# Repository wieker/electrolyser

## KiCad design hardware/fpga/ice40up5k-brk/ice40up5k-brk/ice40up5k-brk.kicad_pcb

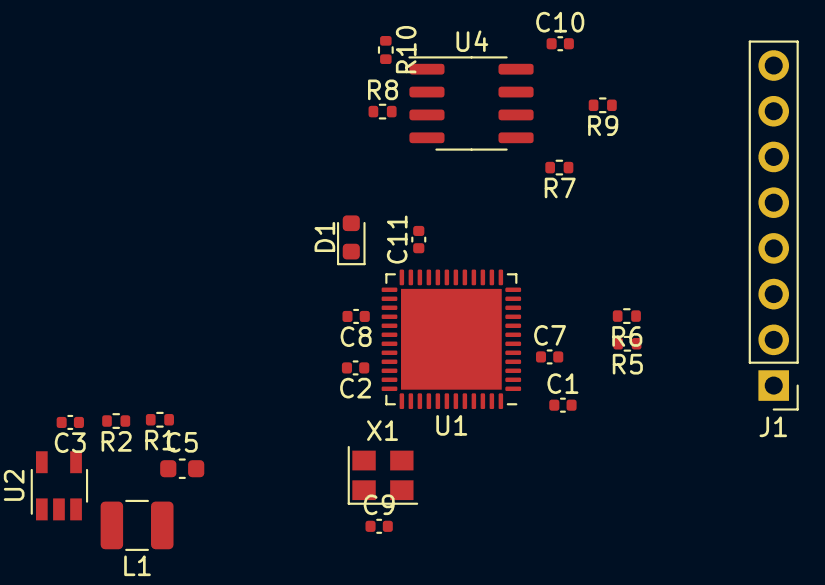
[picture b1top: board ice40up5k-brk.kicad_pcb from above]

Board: 2 copper layers, 24 parts (0 on the bottom side), 13 nets, no tracks yet.

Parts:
C1, C2, C7, C8, C10, C11: 0.1uF; C_0402_1005Metric
C3: 4.7uF; C_0402_1005Metric
C5: 10uF; C_0603_1608Metric
C9: 0.01uF; C_0402_1005Metric
D1: CDBU0520; D_0603_1608Metric
J1: Conn_01x08_Male; PinHeader_1x08_P2.54mm_Vertical
L1: L; L_1210_3225Metric
R1, R2, R5, R6, R7, R8, R9, R10: 100kOhm; R_0402_1005Metric
U1: ICE40UP5K-SG48ITR; QFN-48-1EP_7x7mm_P0.5mm_EP5.6x5.6mm
U2: LTC3406ES5; TSOT-23-5
U4: AT25SF081-SSHD-X; SOIC-8_3.9x4.9mm_P1.27mm
X1: ASE-xxxMHz; Oscillator_SMD_Abracon_ASE-4Pin_3.2x2.5mm

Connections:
+1V2: C5.1, C7.1, C8.1, L1.1, R1.1, U1.5, U1.29, U1.30
+3V3: C1.1, C2.1, C3.1, C9.1, C10.1, C11.1, D1.2, J1.1, R5.1, R6.1, R7.1, R8.1, R9.1, R10.1, U1.1, U1.22, U1.33, U2.1, U2.4, U4.8, X1.1, X1.4
GND: C1.2, C2.2, C3.2, C5.2, C7.2, C8.2, C9.2, C10.2, C11.2, J1.8, R2.2, U1.49, U2.2, U4.4, X1.2
unnamed: D1.1, U1.24
unnamed: L1.2, U2.3
unnamed: R1.2, R2.1, U2.5
cdone: J1.2, R5.2, U1.7
clk: U1.37, X1.3
creset: J1.3, R6.2, U1.8
miso: J1.6, R8.2, U1.14, U4.2
mosi: J1.7, R7.2, U1.17, U4.5
sck: J1.4, R9.2, U1.15, U4.6
ss: J1.5, R10.2, U1.16, U4.1

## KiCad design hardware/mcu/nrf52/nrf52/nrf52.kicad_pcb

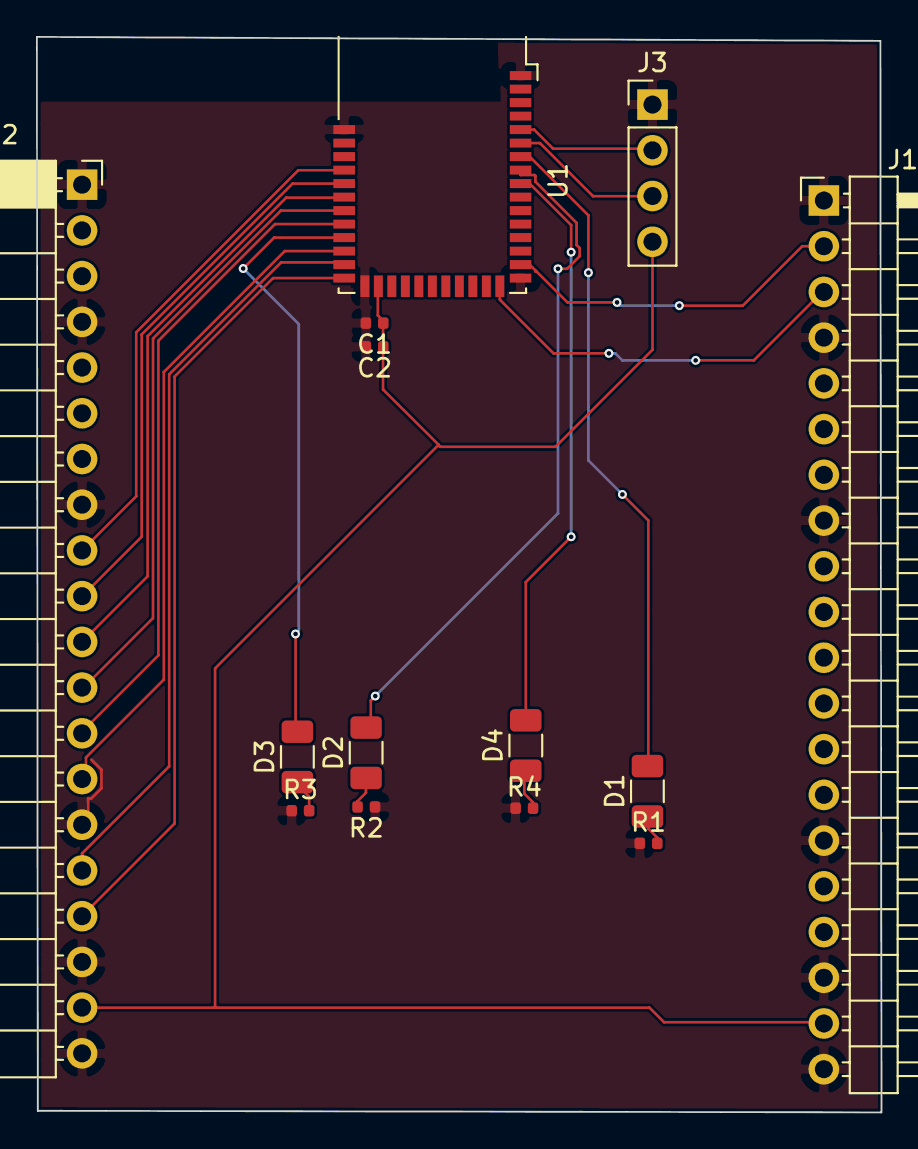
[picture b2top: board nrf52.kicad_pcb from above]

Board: 2 copper layers, 46.9 x 59.8 mm, 14 parts (0 on the bottom side), 22 nets.

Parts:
C1: 0.1uF; C_0402_1005Metric
C2: 4.7uF; C_0402_1005Metric
D1, D2, D3, D4: LED; C_1206_3216Metric
J1: Conn_01x20_Female; PinHeader_1x20_P2.54mm_Horizontal
J2: Conn_01x20_Male; PinSocket_1x20_P2.54mm_Horizontal
J3: Conn_01x04_Male; PinHeader_1x04_P2.54mm_Vertical
R1, R2, R3, R4: 10kOhm; R_0402_1005Metric
U1: BL652; Laird_BL652

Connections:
+3V3: C1.1, C2.1, J1.19, J2.19, J3.4, U1.26
GND: C1.2, C2.2, J1.1, J1.4, J1.8, J1.15, J1.18, J1.20, J2.1, J2.4, J2.8, J2.15, J2.18, J2.20, J3.1, R1.1, R2.1, R3.1, R4.1, U1.1, U1.16, U1.27, U1.39
unnamed: D1.1, R1.2
unnamed: D1.2, U1.7
unnamed: D2.1, R2.2
unnamed: D2.2, U1.8
unnamed: D3.1, R3.2
unnamed: D3.2, U1.31
unnamed: D4.1, R4.2
unnamed: D4.2, U1.9
unnamed: J1.2, U1.15
unnamed: J1.3, U1.17
unnamed: J2.9, U1.36
unnamed: J2.10, U1.35
unnamed: J2.11, U1.34
unnamed: J2.12, U1.33
unnamed: J2.13, U1.32
unnamed: J2.14, U1.30
unnamed: J2.16, U1.29
unnamed: J2.17, U1.28
unnamed: J3.2, U1.5
unnamed: J3.3, U1.6

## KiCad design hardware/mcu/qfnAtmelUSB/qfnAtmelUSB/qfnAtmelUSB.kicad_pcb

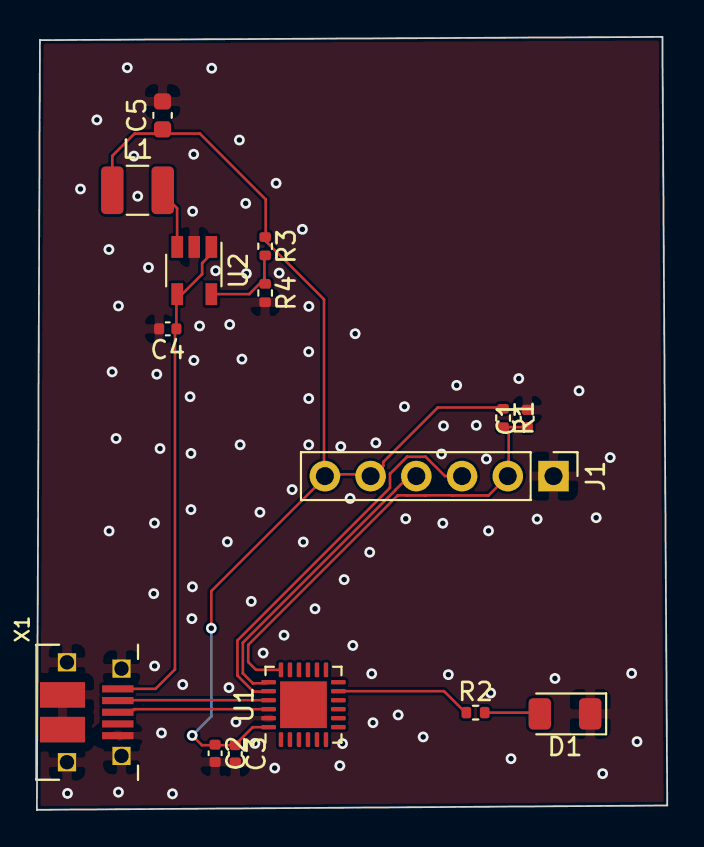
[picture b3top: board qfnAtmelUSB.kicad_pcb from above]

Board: 2 copper layers, 35.0 x 42.9 mm, 15 parts (0 on the bottom side), 12 nets.

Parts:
C1, C3: 0.1uF; C_0402_1005Metric
C2, C4: 4.7uF; C_0402_1005Metric
C5: 10uF; C_0603_1608Metric
D1: LED; LED_1206_3216Metric
J1: Conn_01x06_Male; PinHeader_1x06_P2.54mm_Vertical
L1: L; L_1210_3225Metric
R1, R2: 10kOhm; R_0402_1005Metric
R3: 450kOhm; R_0402_1005Metric
R4: 100kOhm; R_0402_1005Metric
U1: ATSAMD11D14A-M; QFN-24-1EP_4x4mm_P0.5mm_EP2.6x2.6mm
U2: LTC3406ES5; TSOT-23-5
X1: USBFCI_10103594_MILL; FCI_10103594_MILL

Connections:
+3V3: C2.1, C3.1, C5.1, J1.5, J1.6, L1.1, R1.1, R3.1, U1.24
+5V: C4.1, U2.1, U2.4, X1.VBUS
GND: C1.2, C2.2, C3.2, C4.2, C5.2, D1.1, J1.1, R4.2, U1.23, U2.2, X1.BASE@1, X1.BASE@2, X1.GND, X1.SPRT@1, X1.SPRT@2, X1.SPRT@3, X1.SPRT@4
unnamed: D1.2, R2.2
unnamed: L1.2, U2.3
unnamed: R3.2, R4.1, U2.5
unnamed: U1.21, X1.D-
unnamed: U1.22, X1.D+
led_mcu: R2.1, U1.11
swd_clk: J1.4, U1.19
swd_io: J1.3, U1.20
swd_rst: C1.1, J1.2, R1.2, U1.18

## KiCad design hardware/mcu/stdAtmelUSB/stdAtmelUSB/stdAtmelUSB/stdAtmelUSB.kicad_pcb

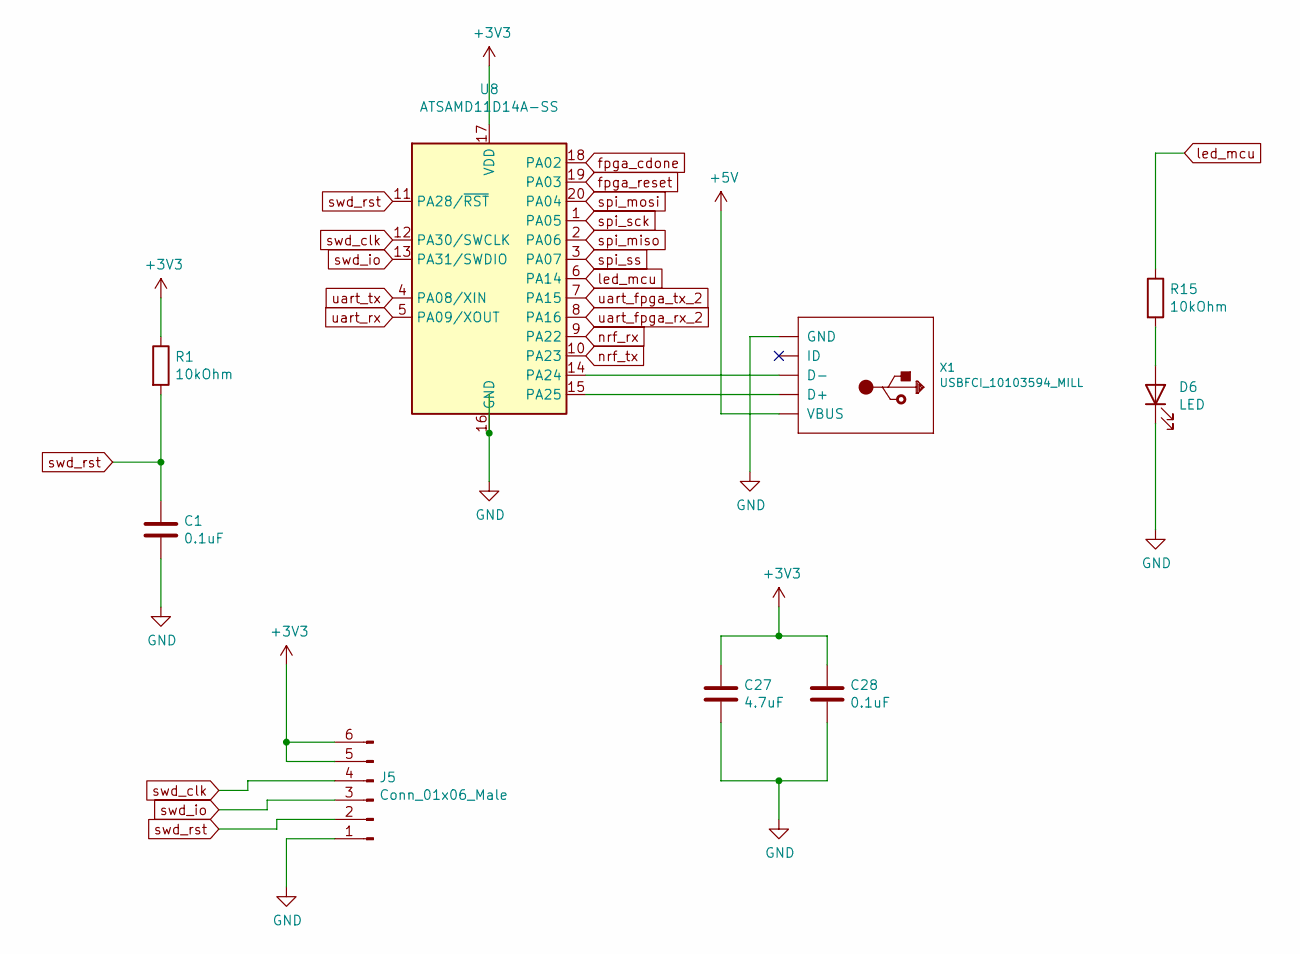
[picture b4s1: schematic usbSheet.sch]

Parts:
C1, C28: 0.1uF; C_0402_1005Metric
C27: 4.7uF; C_0402_1005Metric
D6: LED; LED_1206_3216Metric
J5: Conn_01x06_Male; PinHeader_1x06_P2.54mm_Vertical
R1, R15: 10kOhm; R_0402_1005Metric
U8: ATSAMD11D14A-SS; SOIC-20W_7.5x12.8mm_P1.27mm
X1: USBFCI_10103594_MILL; FCI_10103594_MILL

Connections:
+3V3: C27.1, C28.1, J5.5, J5.6, R1.1, U8.17 (VDD); also elsewhere on the board
+5V: X1.VBUS; also elsewhere on the board
GND: C1.2, C27.2, C28.2, D6.1 (K), J5.1, U8.16 (GND), X1.BASE@1 (GND), X1.BASE@2 (GND), X1.GND, X1.SPRT@1 (GND), X1.SPRT@2 (GND), X1.SPRT@3 (GND), X1.SPRT@4 (GND); also elsewhere on the board
unnamed: D6.2 (A), R15.2
unnamed: U8.14 (PA24), X1.D-
unnamed: U8.15 (PA25), X1.D+
fpga_cdone: U8.18 (PA02); also elsewhere on the board
fpga_reset: U8.19 (PA03); also elsewhere on the board
led_mcu: R15.1, U8.6 (PA14)
nrf_rx: U8.9 (PA22); also elsewhere on the board
nrf_tx: U8.10 (PA23); also elsewhere on the board
spi_miso: U8.2 (PA06); also elsewhere on the board
spi_mosi: U8.20 (PA04); also elsewhere on the board
spi_sck: U8.1 (PA05); also elsewhere on the board
spi_ss: U8.3 (PA07); also elsewhere on the board
swd_clk: J5.4, U8.12 (PA30/SWCLK)
swd_io: J5.3, U8.13 (PA31/SWDIO)
swd_rst: C1.1, J5.2, R1.2, U8.11 (PA28/~RST)
uart_fpga_rx_2: U8.8 (PA16); also elsewhere on the board
uart_fpga_tx_2: U8.7 (PA15); also elsewhere on the board
uart_rx: U8.5 (PA09/XOUT); also elsewhere on the board
uart_tx: U8.4 (PA08/XIN); also elsewhere on the board

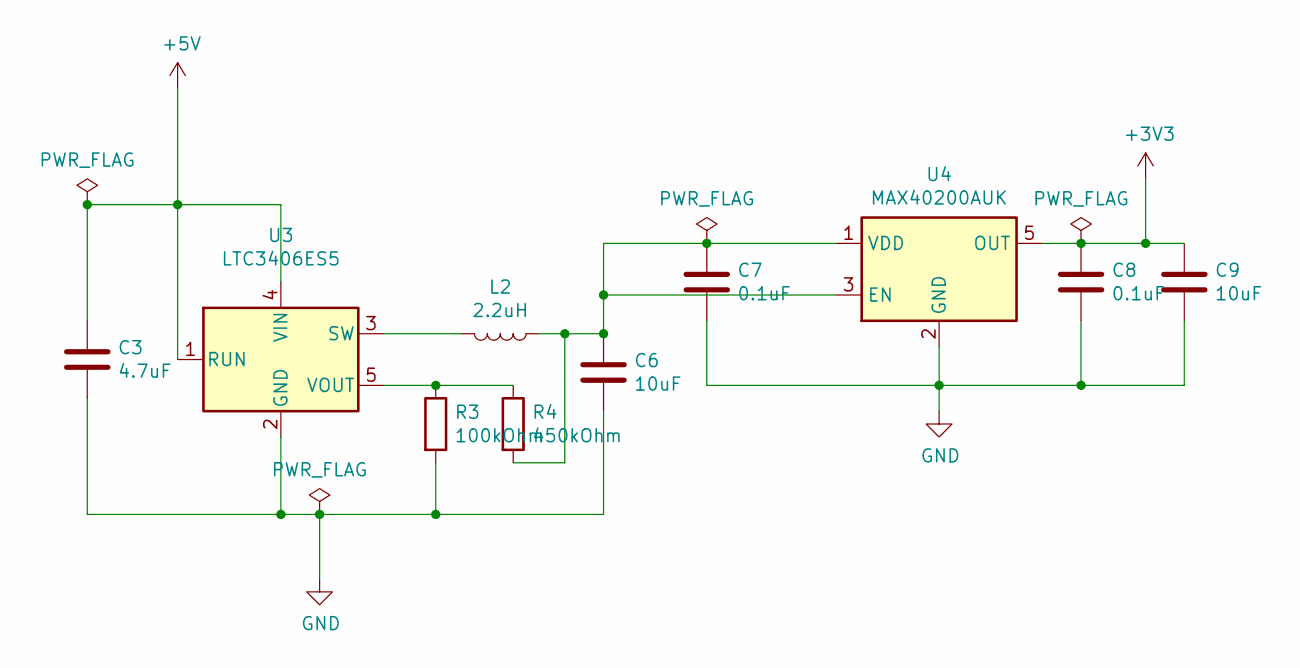
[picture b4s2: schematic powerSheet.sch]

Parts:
C3: 4.7uF; C_0402_1005Metric
C6, C9: 10uF; C_0603_1608Metric
C7, C8: 0.1uF; C_0402_1005Metric
L2: 2.2uH; L_0805_2012Metric
R3: 100kOhm; R_0402_1005Metric
R4: 450kOhm; R_0402_1005Metric
U3: LTC3406ES5; TSOT-23-5
U4: MAX40200AUK; SOT-23-5

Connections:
+3V3: C8.1, C9.1, U4.5 (OUT); also elsewhere on the board
+5V: C3.1, U3.1 (RUN), U3.4 (VIN); also elsewhere on the board
GND: C3.2, C6.2, C7.2, C8.2, C9.2, R3.2, U3.2 (GND), U4.2 (GND); also elsewhere on the board
unnamed: C6.1, C7.1, L2.1, R4.2, U4.1 (VDD), U4.3 (EN)
unnamed: L2.2, U3.3 (SW)
unnamed: R3.1, R4.1, U3.5 (VOUT)

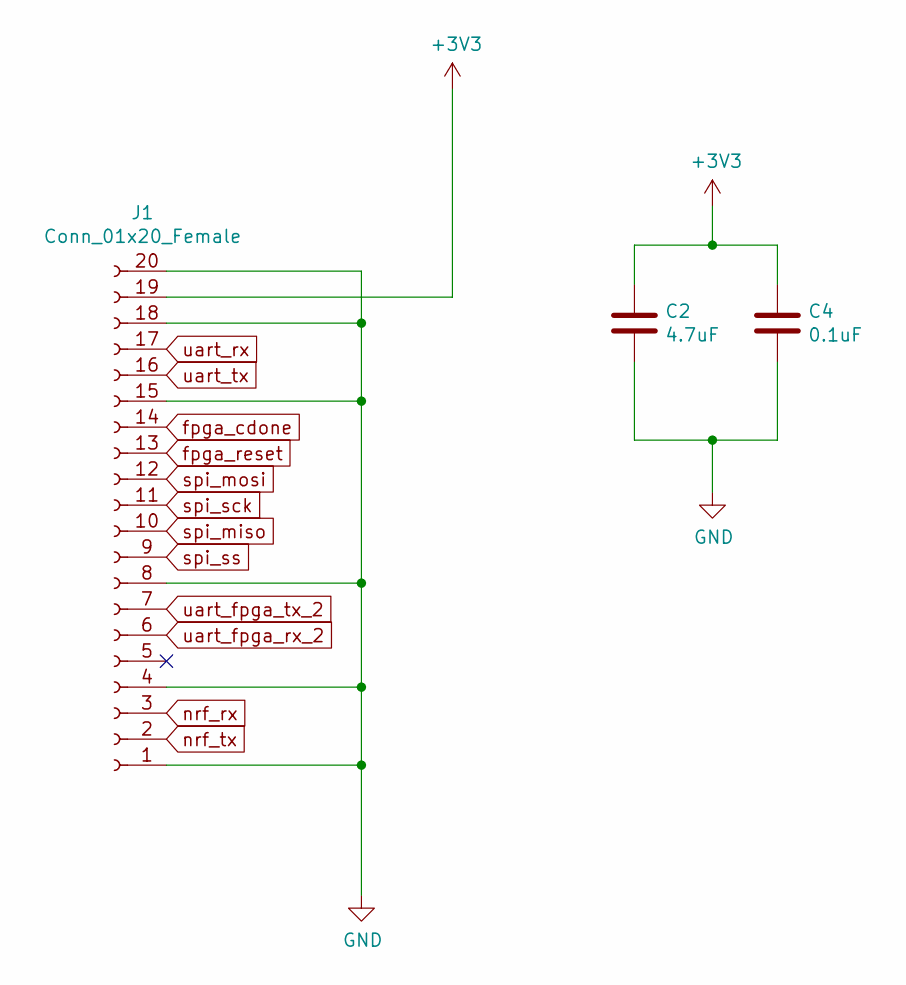
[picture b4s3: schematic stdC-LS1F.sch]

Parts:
C2: 4.7uF; C_0402_1005Metric
C4: 0.1uF; C_0402_1005Metric
J1: Conn_01x20_Female; PinHeader_1x20_P2.54mm_Horizontal

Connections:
+3V3: C2.1, C4.1, J1.19; also elsewhere on the board
GND: C2.2, C4.2, J1.1, J1.4, J1.8, J1.15, J1.18, J1.20; also elsewhere on the board
fpga_cdone: J1.14; also elsewhere on the board
fpga_reset: J1.13; also elsewhere on the board
nrf_rx: J1.3; also elsewhere on the board
nrf_tx: J1.2; also elsewhere on the board
spi_miso: J1.10; also elsewhere on the board
spi_mosi: J1.12; also elsewhere on the board
spi_sck: J1.11; also elsewhere on the board
spi_ss: J1.9; also elsewhere on the board
uart_fpga_rx_2: J1.6; also elsewhere on the board
uart_fpga_tx_2: J1.7; also elsewhere on the board
uart_rx: J1.17; also elsewhere on the board
uart_tx: J1.16; also elsewhere on the board

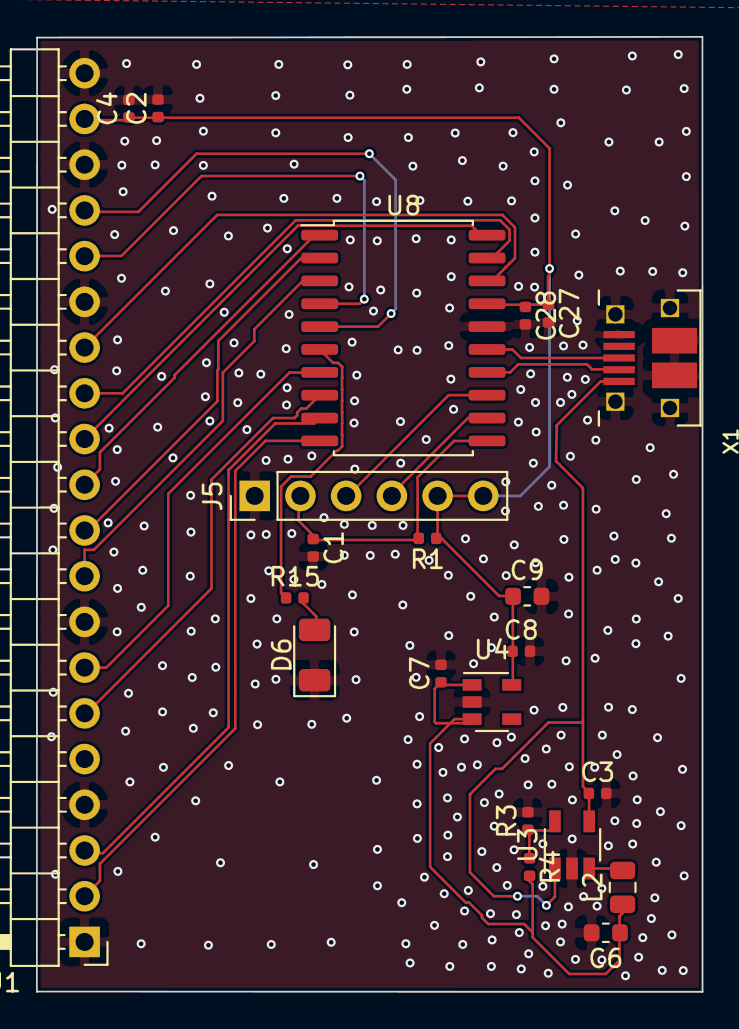
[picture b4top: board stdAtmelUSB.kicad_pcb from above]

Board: 2 copper layers, 37.0 x 53.0 mm, 22 parts (0 on the bottom side), 25 nets.
